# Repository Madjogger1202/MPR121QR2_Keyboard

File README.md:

# MPR121QR2_Keyboard

**Мини-клавиатура на 12 сенсорных кнопок: ёмкостный драйвер MPR121QR2, контроллер RP2040 и цветной дисплей ST7735.**

Компактная плата сенсорной клавиатуры на базе контроллера касаний **MPR121QR2** (NXP), обслуживающего 12 ёмкостных кнопок по I²C. Логику и обработку берёт на себя **RP2040**, для индикации установлен дисплей **0.96" ST7735**, а на борту есть узел измерения тока. Завершающая плата небольшой серии проектов на RP2040.

## Обзор

- **Название проекта:** MPR121QR2_Keyboard
- **Контроллер касаний:** NXP MPR121QR2 — 12-канальный ёмкостный сенсор (I²C)
- **Микроконтроллер:** Raspberry Pi RP2040 (двухъядерный Cortex-M0+)
- **Дисплей:** 0.96" ST7735 (цветной TFT, SPI)
- **Доп. функция:** измерение тока на плате
- **Назначение:** сенсорная клавиатура / ввод касанием, эксперименты с ёмкостными кнопками

## Ключевые особенности

- **12 ёмкостных кнопок** — MPR121QR2 обслуживает до 12 сенсорных электродов с автоконфигурацией и настраиваемыми порогами
- **I²C-интерфейс + IRQ** — компактное подключение, прерывание по событию касания
- **RP2040** — двухъядерный Arm Cortex-M0+ до 133 МГц, обработка касаний и вывод на дисплей
- **Цветной дисплей 0.96" ST7735** — индикация состояния кнопок и данных по SPI
- **Измерение тока** — узел контроля потребления на плате
- **Доступная элементная база** — MPR121 широко доступен, готовый модуль с ним стоит около 100 руб, так что решение легко повторить

## Что на плате

| Блок | Компонент | Назначение |
|---|---|---|
| Контроллер касаний | MPR121QR2 | 12 ёмкостных кнопок по I²C |
| Микроконтроллер | RP2040 | Обработка касаний, логика, вывод на дисплей |
| Дисплей | 0.96" ST7735 | Цветной TFT-индикатор (SPI) |
| Измерение тока | узел токового контроля | Замер потребления |
| Интерфейс | USB | Питание и связь с хостом |

## Технические характеристики

| Параметр | Значение |
|---|---|
| Контроллер касаний | NXP MPR121QR2, 12 электродов |
| Интерфейс сенсора | I²C (до 400 кГц) + линия IRQ |
| Микроконтроллер | RP2040, 2× Cortex-M0+ до 133 МГц |
| Дисплей | 0.96" ST7735, цветной TFT, SPI |
| Измерение тока | встроенный узел |
| Питание | USB / 3.3 В |

## Применение

- Сенсорная клавиатура / панель ввода касанием
- Изучение ёмкостных кнопок и контроллера MPR121
- Компактный пользовательский интерфейс с индикацией на дисплее
- Учебная/макетная плата на RP2040

## Среда разработки

- **Схема и плата:** KiCad
- **Прошивка:** PlatformIO / Arduino / Pico SDK (RP2040)
- **Документация на компоненты:** datasheet MPR121 (NXP), RP2040 (Raspberry Pi), ST7735

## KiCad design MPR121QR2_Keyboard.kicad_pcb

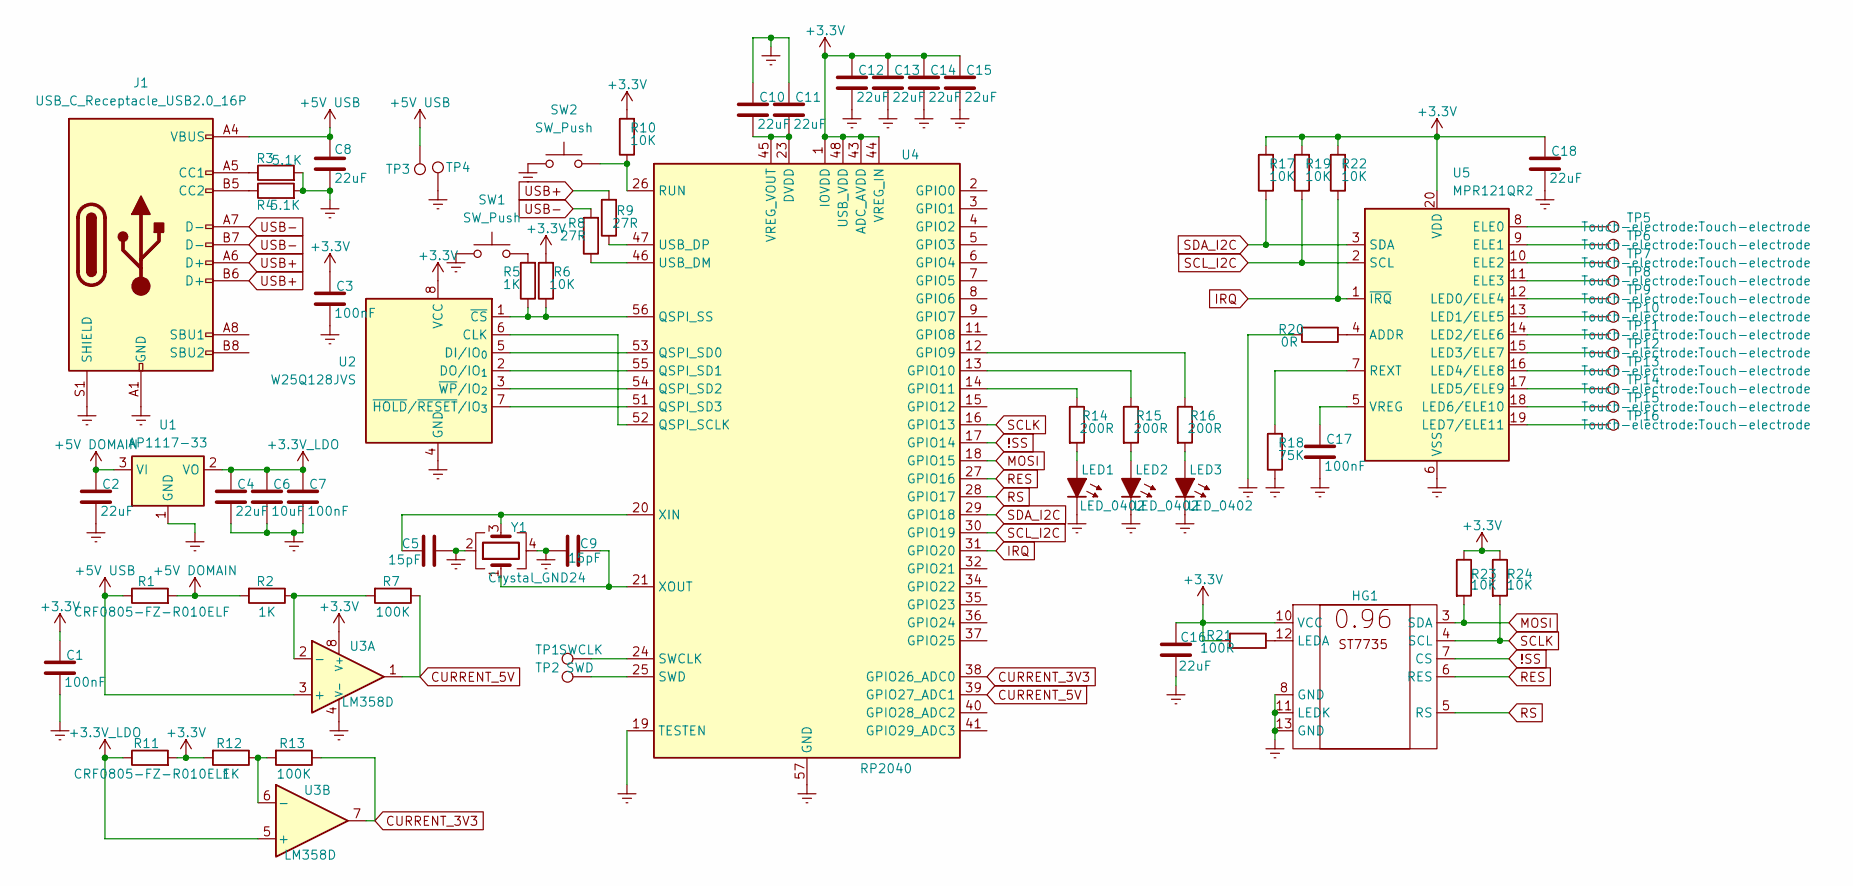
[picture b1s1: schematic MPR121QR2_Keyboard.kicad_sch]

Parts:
C1, C3, C7, C17: 100nF; C_0402_1005Metric
C2, C4, C8, C10, C11, C12, C13, C14, C15, C16, C18: 22uF; C_0402_1005Metric
C5, C9: 15pF; C_0402_1005Metric
C6: 10uF; C_0402_1005Metric
HG1: ST7735 0.96
J1: USB_C_Receptacle_USB2.0_16P; USB_C_Receptacle_GCT_USB4105-xx-A_16P_TopMnt_Horizontal
LED1, LED2, LED3: LED_0402; LED_0402_1005Metric
R1: CRF0805-FZ-R010ELF; R_0805_2012Metric_Pad1.15x1.40mm
R2, R5, R12: 1K; R_0402_1005Metric
R3, R4: 5.1K; R_0402_1005Metric
R6, R10, R17, R19, R22, R23, R24: 10K; R_0402_1005Metric
R7, R13: 100K; R_0402_1005Metric
R8, R9: 27R; R_0402_1005Metric
R11: CRF0805-FZ-R010ELF; R_0805_2012Metric
R14, R15, R16: 200R; R_0402_1005Metric
R18: 75K; R_0402_1005Metric
R20: 0R; R_0402_1005Metric
R21: 100R; R_0402_1005Metric
SW1, SW2: SW_Push; SW_SPST_B3U-1000P
TP1: SWCLK; TestPoint_Pad_D1.0mm
TP2: SWD; TestPoint_Pad_D1.0mm
TP3, TP4: TestPoint_Pad_1.5x1.5mm
TP5, TP6, TP7, TP8, TP9, TP10, TP11, TP12, TP13, TP14, TP15, TP16: TestPoint; Touch-electrode
U1: AP1117-33; SOT-223-3_TabPin2
U2: W25Q128JVS; SOIC-8_5.3x5.3mm_P1.27mm
U3: LM358D; SO-8_3.9x4.9mm_P1.27mm
U4: RP2040; QFN-56-1EP_7x7mm_P0.4mm_EP3.2x3.2mm
U5: MPR121QR2; UQFN-20_3x3mm_P0.4mm
Y1: Crystal_GND24; Crystal_SMD_Abracon_ABM8G-4Pin_3.2x2.5mm

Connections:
!SS: HG1.7 (CS), U4.17 (GPIO14)
+3.3V: C1.1, C3.1, C12.1, C13.1, C14.1, C15.1, C16.1, C18.1, HG1.10 (VCC), R6.2, R10.2, R11.2, R12.2, R17.2, R19.2, R21.2, R22.2, R23.1, R24.1, U2.8 (VCC), U3.8 (V+), U4.1 (IOVDD), U4.10 (IOVDD), U4.22 (IOVDD), U4.33 (IOVDD), U4.42 (IOVDD), U4.43 (ADC_AVDD), U4.44 (VREG_IN), U4.48 (USB_VDD), U4.49 (IOVDD), U5.20 (VDD)
+3.3V_LDO: C4.1, C6.1, C7.1, R11.1, U1.2 (VO), U3.5 (+)
+5V DOMAIN: C2.1, R1.2, R2.2, U1.3 (VI)
+5V USB: C8.1, J1.A4 (VBUS), J1.A9 (VBUS), J1.B4 (VBUS), J1.B9 (VBUS), R1.1, TP3.1, U3.3 (+); also elsewhere on the board
CURRENT_3V3: R13.1, U3.7, U4.38 (GPIO26_ADC0)
CURRENT_5V: R7.1, U3.1, U4.39 (GPIO27_ADC1)
Earth: C1.2, C2.2, C3.2, C4.2, C5.2, C6.2, C7.2, C8.2, C9.1, C10.1, C11.1, C12.2, C13.2, C14.2, C15.2, C16.2, C17.2, C18.2, HG1.8 (GND), HG1.11 (LEDK), HG1.13 (GND), J1.A1 (GND), J1.A12 (GND), J1.B1 (GND), J1.B12 (GND), J1.S1 (SHIELD), LED1.1 (K), LED2.1 (K), LED3.1 (K), R3.2, R4.2, R18.1, R20.2, SW1.1, SW2.1, TP4.1, U1.1 (GND), U2.4 (GND), U3.4 (V-), U4.19 (TESTEN), U4.57 (GND), U5.6 (VSS), Y1.2, Y1.4; also elsewhere on the board
IRQ: R22.1, U4.31 (GPIO20), U5.1 (~IRQ)
MOSI: HG1.3 (SDA), R23.2, U4.18 (GPIO15)
unnamed: HG1.12 (LEDA), R21.1
unnamed: J1.A5 (CC1), R3.1
unnamed: J1.B5 (CC2), R4.1
unnamed: LED1.2 (A), R14.2
unnamed: LED2.2 (A), R15.2
unnamed: LED3.2 (A), R16.2
unnamed 16: R5.2, SW1.2; also elsewhere on the board
unnamed: U2.6 (CLK), U4.52 (QSPI_SCLK)
unnamed: U2.5 (DI/IO_{0}), U4.53 (QSPI_SD0)
unnamed: U2.2 (DO/IO_{1}), U4.55 (QSPI_SD1)
unnamed: R5.1, R6.1, U2.1 (~CS), U4.56 (QSPI_SS)
unnamed: U2.7 (~HOLD/~RESET/IO_{3}), U4.51 (QSPI_SD3)
unnamed: U2.3 (~WP/IO_{2}), U4.54 (QSPI_SD2)
unnamed: R2.1, R7.2, U3.2 (-)
unnamed: R12.1, R13.2, U3.6 (-)
unnamed: R16.1, U4.12 (GPIO9)
unnamed: R15.1, U4.13 (GPIO10)
unnamed: R14.1, U4.14 (GPIO11)
unnamed 28: R10.1, SW2.2, U4.26 (RUN); also elsewhere on the board
unnamed 29: TP1.1, U4.24 (SWCLK); also elsewhere on the board
unnamed 30: TP2.1, U4.25 (SWD); also elsewhere on the board
unnamed: R8.1, U4.46 (USB_DM)
unnamed: R9.1, U4.47 (USB_DP)
unnamed: C10.2, C11.2, U4.23 (DVDD), U4.45 (VREG_VOUT), U4.50 (DVDD)
unnamed: C5.1, U4.20 (XIN), Y1.3
unnamed: C9.2, U4.21 (XOUT), Y1.1
unnamed: R20.1, U5.4 (ADDR)
unnamed: TP5.1, U5.8 (ELE0)
unnamed: TP6.1, U5.9 (ELE1)
unnamed: TP7.1, U5.10 (ELE2)
unnamed: TP8.1, U5.11 (ELE3)
unnamed: TP9.1, U5.12 (LED0/ELE4)
unnamed: TP10.1, U5.13 (LED1/ELE5)
unnamed: TP11.1, U5.14 (LED2/ELE6)
unnamed: TP12.1, U5.15 (LED3/ELE7)
unnamed: TP13.1, U5.16 (LED4/ELE8)
unnamed: TP14.1, U5.17 (LED5/ELE9)
unnamed: TP15.1, U5.18 (LED6/ELE10)
unnamed: TP16.1, U5.19 (LED7/ELE11)
unnamed: R18.2, U5.7 (REXT)
unnamed: C17.1, U5.5 (VREG)
RES: HG1.6 (RES), U4.27 (GPIO16)
RS: HG1.5 (RS), U4.28 (GPIO17)
SCLK: HG1.4 (SCL), R24.2, U4.16 (GPIO13)
SCL_I2C: R19.1, U4.30 (GPIO19), U5.2 (SCL)
SDA_I2C: R17.1, U4.29 (GPIO18), U5.3 (SDA)
USB+: J1.A6 (D+), J1.B6 (D+), R9.2
USB-: J1.A7 (D-), J1.B7 (D-), R8.2

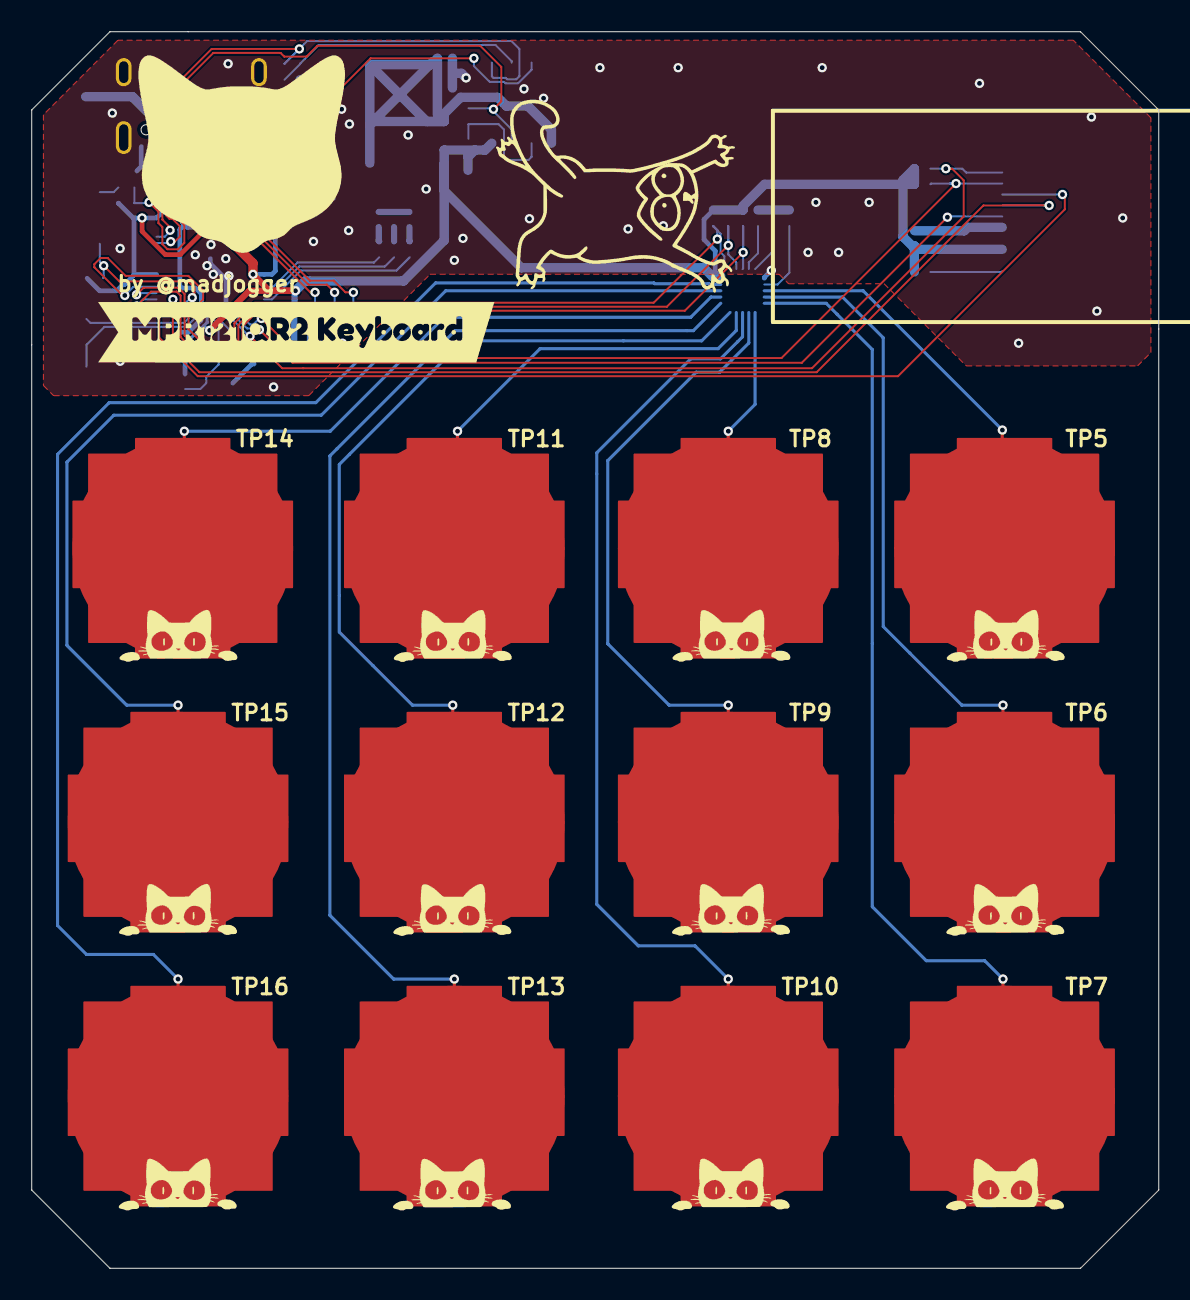
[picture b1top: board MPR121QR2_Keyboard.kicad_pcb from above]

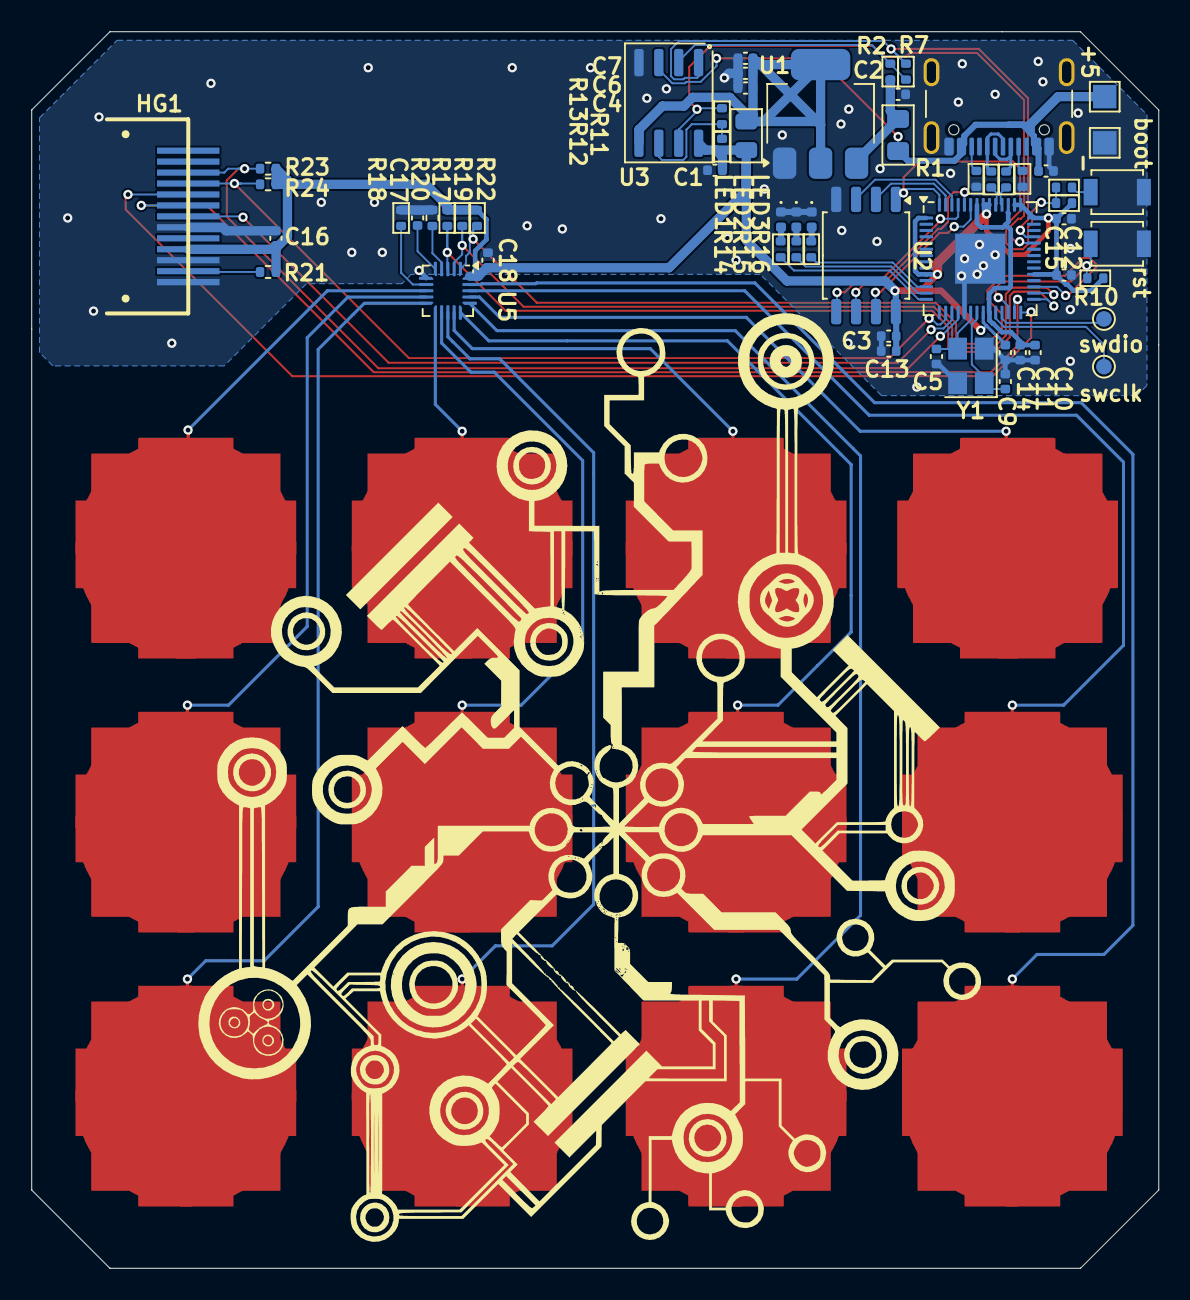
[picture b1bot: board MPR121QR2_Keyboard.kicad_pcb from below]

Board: 2 copper layers, 72.0 x 79.0 mm, 72 parts (59 on the bottom side), 58 nets.

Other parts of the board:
+5: TestPoint_Pad_1.5x1.5mm
-: TestPoint_Pad_1.5x1.5mm
boot: SW_Push; SW_SPST_B3U-1000P
kibuzzard-680FD2EB: G***; kibuzzard-680FD2EB
rst: SW_Push; SW_SPST_B3U-1000P
swclk: SWCLK; TestPoint_Pad_D1.0mm
swdio: SWD; TestPoint_Pad_D1.0mm

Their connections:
+5V USB: +5.1; also elsewhere on the board
Earth: -.1, boot.1, rst.1; also elsewhere on the board
unnamed 16: boot.2; also elsewhere on the board
unnamed 28: rst.2; also elsewhere on the board
unnamed 29: swclk.1; also elsewhere on the board
unnamed 30: swdio.1; also elsewhere on the board

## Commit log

2025-04-28 вроде готова схема и частично плата
2025-04-28 rev0
